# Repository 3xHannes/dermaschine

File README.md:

dermaschine
===========

Software-Repo für der Maschine

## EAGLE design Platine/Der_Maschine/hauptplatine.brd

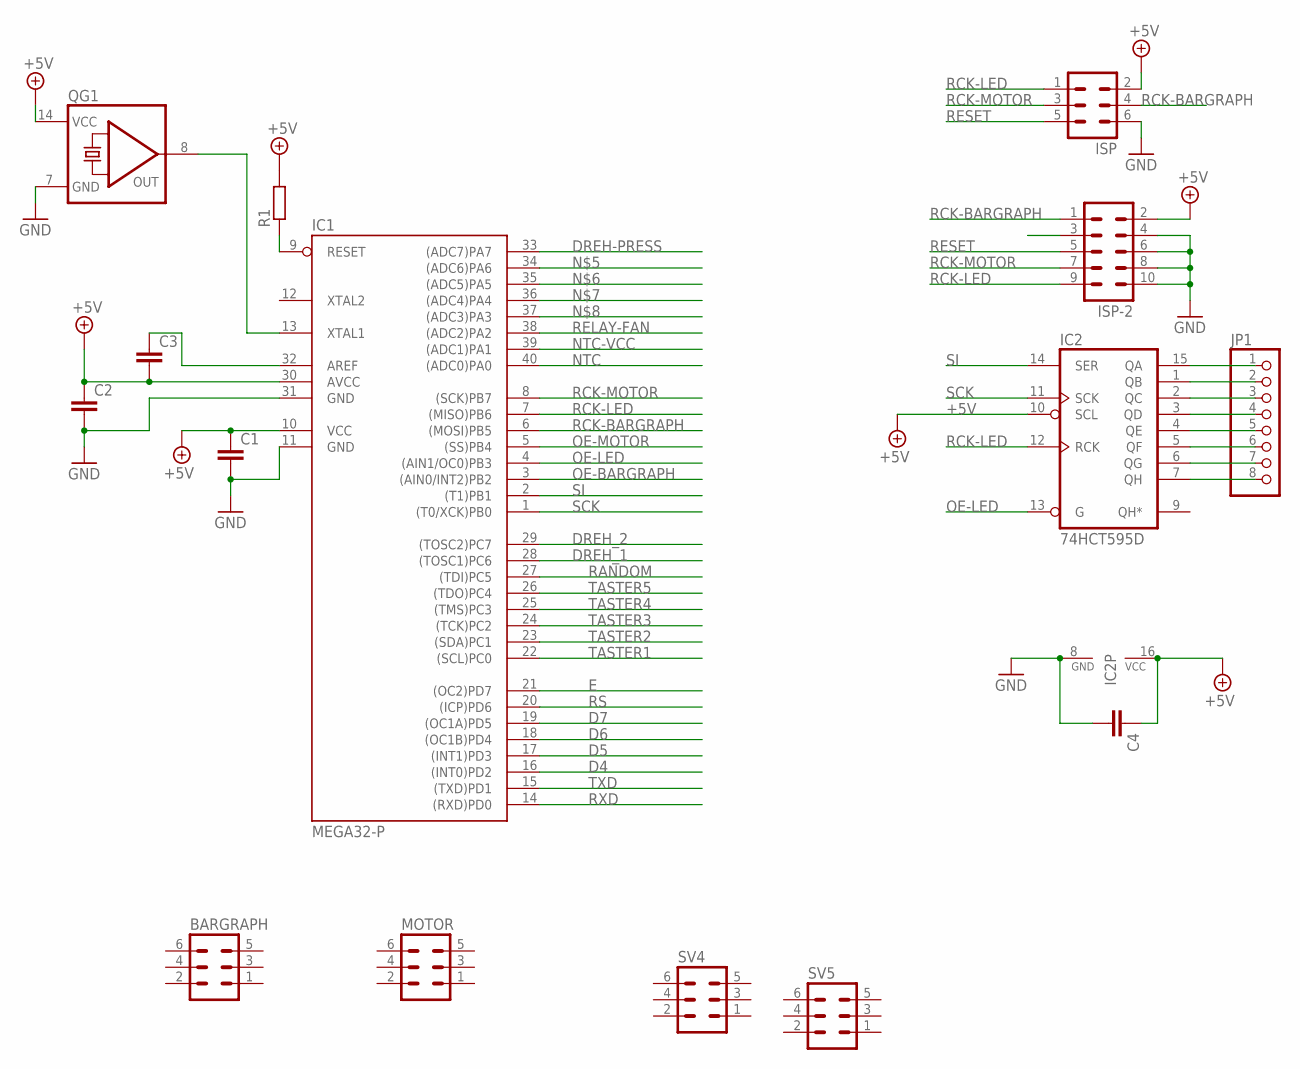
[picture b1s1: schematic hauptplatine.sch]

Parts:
BARGRAPH: ML6
C1, C4: C-EU025-025X050; C025-025X050
C2, C3: C-EUC0805; C0805
IC1: MEGA32-P; DIL40
IC2: 74HCT595D; SO16
ISP: ML6
ISP-2: ML10
JP1: PINHD-1X8; 1X08
MOTOR: ML6
QG1: QG5860; DIL14S
R1: R-EU_0207/10; 0207/10
SV4, SV5: ML6

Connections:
+5V: C1.1, C2.1, C3.2, C4.1, IC1.10 (VCC), IC1.30 (AVCC), IC2.10 (SCL), IC2.16 (VCC), ISP.2, ISP-2.2, QG1.14 (VCC), R1.2
D4: IC1.16 ((INT0)PD2)
D5: IC1.17 ((INT1)PD3)
D6: IC1.18 ((OC1B)PD4)
D7: IC1.19 ((OC1A)PD5)
DREH-PRESS: IC1.33 ((ADC7)PA7)
DREH_1: IC1.28 ((TOSC1)PC6)
DREH_2: IC1.29 ((TOSC2)PC7)
E: IC1.21 ((OC2)PD7)
GND: C1.2, C2.2, C4.2, IC1.11 (GND), IC1.31 (GND), IC2.8 (GND), ISP.6, ISP-2.4, ISP-2.6, ISP-2.8, ISP-2.10, QG1.7 (GND)
unnamed: IC1.13 (XTAL1), QG1.8 (OUT)
unnamed: IC2.15 (QA), JP1.1
unnamed: IC2.1 (QB), JP1.2
unnamed: C3.1, IC1.32 (AREF)
unnamed: IC2.2 (QC), JP1.3
unnamed: IC2.3 (QD), JP1.4
unnamed: IC2.4 (QE), JP1.5
unnamed: IC2.5 (QF), JP1.6
unnamed: IC2.6 (QG), JP1.7
unnamed: IC2.7 (QH), JP1.8
NTC: IC1.40 ((ADC0)PA0)
NTC-VCC: IC1.39 ((ADC1)PA1)
OE-BARGRAPH: IC1.3 ((AIN0/INT2)PB2)
OE-LED: IC1.4 ((AIN1/OC0)PB3), IC2.13 (G)
OE-MOTOR: IC1.5 ((SS)PB4)
RANDOM: IC1.27 ((TDI)PC5)
RCK-BARGRAPH: IC1.6 ((MOSI)PB5), ISP.4, ISP-2.1
RCK-LED: IC1.7 ((MISO)PB6), IC2.12 (RCK), ISP.1, ISP-2.9
RCK-MOTOR: IC1.8 ((SCK)PB7), ISP.3, ISP-2.7
RELAY-FAN: IC1.38 ((ADC2)PA2)
RESET: IC1.9 (RESET), ISP.5, ISP-2.5, R1.1
RS: IC1.20 ((ICP)PD6)
RXD: IC1.14 ((RXD)PD0)
SCK: IC1.1 ((T0/XCK)PB0), IC2.11 (SCK)
SI: IC1.2 ((T1)PB1), IC2.14 (SER)
TASTER1: IC1.22 ((SCL)PC0)
TASTER2: IC1.23 ((SDA)PC1)
TASTER3: IC1.24 ((TCK)PC2)
TASTER4: IC1.25 ((TMS)PC3)
TASTER5: IC1.26 ((TDO)PC4)
TXD: IC1.15 ((TXD)PD1)

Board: 2 copper layers, 15 parts (3 on the bottom side), 19 nets, no tracks yet.

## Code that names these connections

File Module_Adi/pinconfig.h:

/*
 * pinconfig.h
 *
 * Created: 12.08.2014 18:32:12
 *  Author: Adrian
 */ 

// Pin-Configuration des ATMEGA32

#ifndef PINCONFIG_H_
#define PINCONFIG_H_

// Shift-Register: Port und Pins
#define PORTSR		PORTB
#define SCK			PB0
#define SI			PB1
#define OE_Bargrpah	PB2		// !OE = !G
#define OE_LED		PB3		// !OE = !G
#define OE_Motor	PB4		// !OE = !G
#define RCK_Bargraph PB5
#define RCK_LED		PB6
#define RCK_Motor	PB7

#endif /* PINCONFIG_H_ */

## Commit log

2014-07-12 Auswertung fuer Drehimpulsgeber hinzugefuegt
2014-07-15 LCD Routine erweitert
2014-07-15 Nur Test
2014-07-15 Basic git befehle hinzugefuegt
2014-07-22 kleine aenderung Drehimpulsgeber makro hinzugefuegt und bug behoben
2014-07-28 git basics um schritt-fuer-schritt anleitung erweitert
2014-07-28 Pinbelegung fuer Atmega32 als TXT-Datei hinzugefuegt.
2014-07-29 Eagle-Dateien Hauptplatine hinzugefuegt.
2014-07-31 neue Version drehimpulsgeber
2014-07-31 software gesamt
2014-08-01 neue version drehimpulsgeber & nameMenu hinzugefuegt
2014-08-01 Hauptsoftware hinzugefugt
2014-08-03 Mix-Routine hinzugefuegt (Mit Timer2 realisiert)
2014-08-03 Anzeige beim Mischen verbessert
2014-08-12 Pin-Konfiguration (bis jetzt nur Schieberegister-Pins) und Schieberegister-Routinen hochgeladen
